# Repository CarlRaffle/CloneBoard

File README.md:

# CloneBoard
CloneBoard - Designed by Carl Raffle for the Clone R1

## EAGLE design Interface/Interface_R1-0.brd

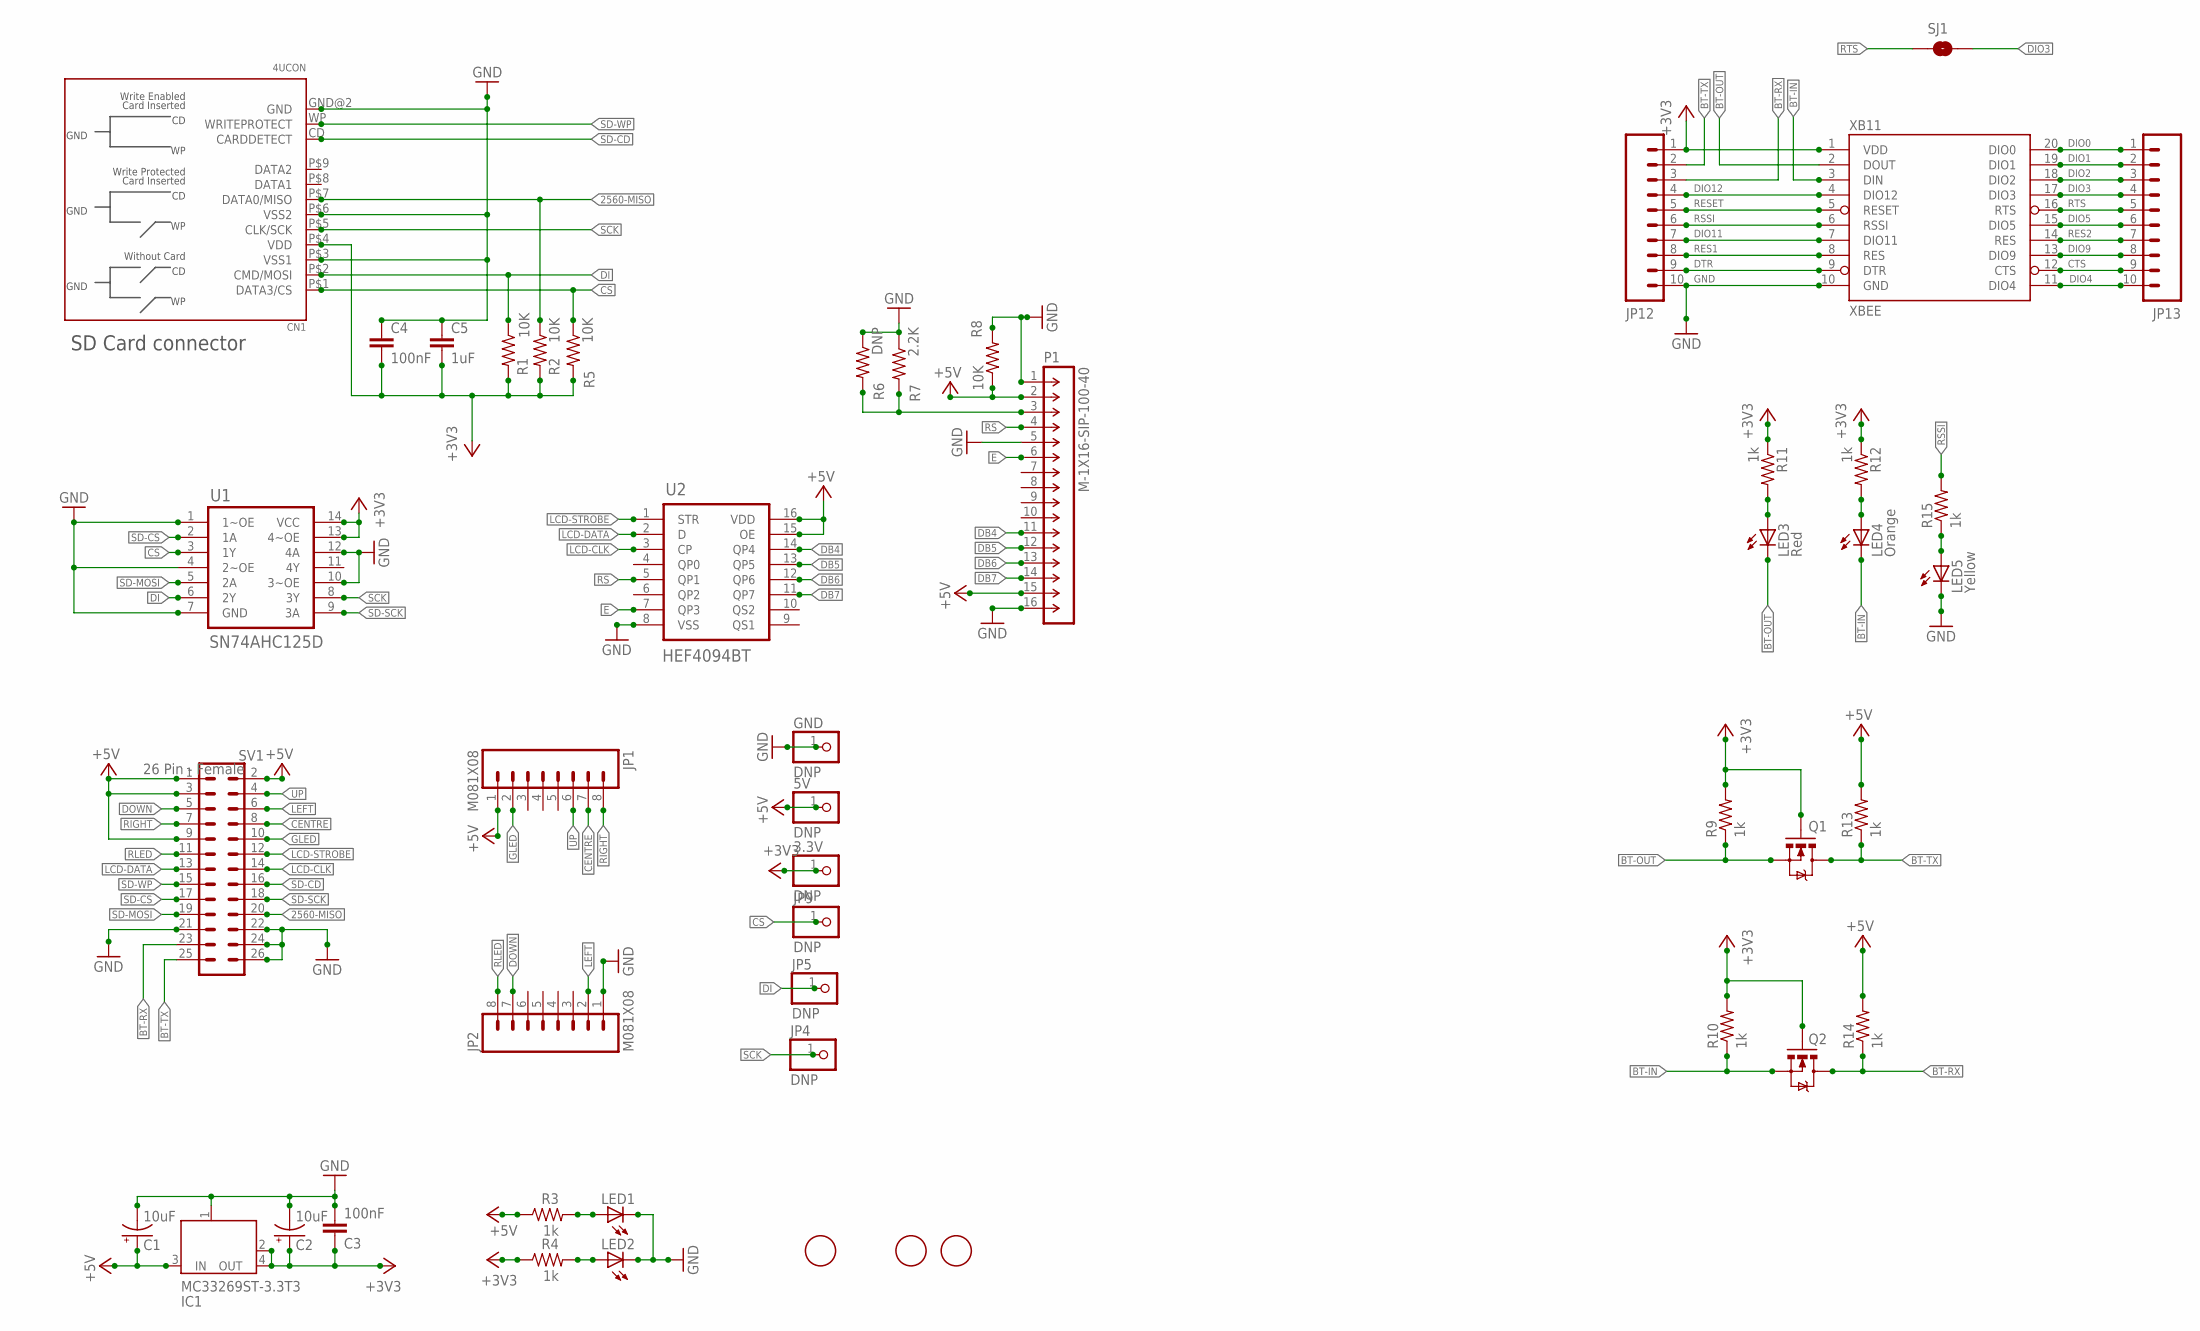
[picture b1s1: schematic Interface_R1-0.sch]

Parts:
3.3V, 5V: DNP; 1X01
C1, C2: 10uF; EIA3216
C3, C4: 100nF; 0805
C5: 1uF; 0805
CN1: 4UCON; SDCARD_SMT_4U19646
GND: DNP; 1X01
IC1: MC33269ST-3.3T3; SOT223
JP1, JP2: M081X08; 1X08
JP3, JP10, JP11: FIDUCIAL1.5X3; FIDUCIAL-1.5X3
JP4, JP5, JP9: DNP; 1X01
JP12, JP13: M100.1; 1X10
LED1: GREEN; LED-0805
LED2: Blue; LED-0805
LED3: Red; LED-0805
LED4: Orange; LED-0805
LED5: Yellow; LED-0805
P1: M-1X16-SIP-100-40; SIP-100-16-40
Q1, Q2: MOSFET-NCHANNELSMD; SOT23-3
R1, R2, R5, R8: 10K; 0805
R3, R4, R9, R10, R11, R12, R13, R14, R15: 1k; 0805
R6: DNP; 0805
R7: 2.2K; 0805
SJ1: SOLDERJUMPERNO; SJ_2S-NO
SV1: 26 Pin - Female; ML26
U1: SN74AHC125D; SOIC127P600X175-14N
U2: HEF4094BT; SOIC127P600X175-16N
XB11: XBEE; XBEE-SILK

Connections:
2560-MISO: CN1.P$7 (DATA0/MISO), R2.1, SV1.20
+3V3: 3.3V.1, C2.A (+), C3.1, C4.2, C5.2, CN1.P$4 (VDD), IC1.2 (OUT), IC1.4 (OUT), JP12.1, Q1.1 (G), Q2.1 (G), R1.2, R2.2, R4.1, R5.2, R9.2, R10.2, R11.1, R12.1, U1.13 (4~OE), U1.14 (VCC), XB11.1 (VDD)
+5V: 5V.1, C1.A (+), IC1.3 (IN), JP1.1, P1.2, P1.15, R3.1, R8.1, R13.2, R14.2, SV1.1, SV1.2, SV1.3, SV1.9, U2.15 (OE), U2.16 (VDD)
BT-IN: LED4.C, Q2.2 (S), R10.1, XB11.3 (DIN)
BT-OUT: LED3.C, Q1.2 (S), R9.1, XB11.2 (DOUT)
BT-RX: JP12.3, Q2.3 (D), R14.1, SV1.23
BT-TX: JP12.2, Q1.3 (D), R13.1, SV1.25
CENTRE: JP1.7, SV1.8
CS: CN1.P$1 (DATA3/CS), JP9.1, R5.1, U1.3 (1Y)
CTS: JP13.9, XB11.12 (CTS)
DB4: P1.11, U2.14 (QP4)
DB5: P1.12, U2.13 (QP5)
DB6: P1.13, U2.12 (QP6)
DB7: P1.14, U2.11 (QP7)
DI: CN1.P$2 (CMD/MOSI), JP5.1, R1.1, U1.6 (2Y)
DIO0: JP13.1, XB11.20 (DIO0)
DIO1: JP13.2, XB11.19 (DIO1)
DIO2: JP13.3, XB11.18 (DIO2)
DIO3: JP13.4, SJ1.2, XB11.17 (DIO3)
DIO4: JP13.10, XB11.11 (DIO4)
DIO5: JP13.6, XB11.15 (DIO5)
DIO9: JP13.8, XB11.13 (DIO9)
DIO11: JP12.7, XB11.7 (DIO11)
DIO12: JP12.4, XB11.4 (DIO12)
DOWN: JP2.7, SV1.5
DTR: JP12.9, XB11.9 (DTR)
E: P1.6, U2.7 (QP3)
GLED: JP1.2, SV1.10
GND: C1.C (-), C2.C (-), C3.2, C4.1, C5.1, CN1.GND@2 (GND), CN1.P$3 (VSS1), CN1.P$6 (VSS2), GND.1, IC1.1 (GND/ADJ), JP2.1, JP12.10, LED1.C, LED2.C, LED5.C, P1.1, P1.5, P1.16, R6.1, R7.1, R8.2, SV1.21, SV1.22, SV1.24, SV1.26, U1.1 (1~OE), U1.4 (2~OE), U1.7 (GND), U1.10 (3~OE), U1.12 (4A), U2.8 (VSS), XB11.10 (GND)
LCD-CLK: SV1.14, U2.3 (CP)
LCD-DATA: SV1.13, U2.2 (D)
LCD-STROBE: SV1.12, U2.1 (STR)
LEFT: JP2.2, SV1.6
unnamed: LED1.A, R3.2
unnamed: LED2.A, R4.2
unnamed: LED3.A, R11.2
unnamed: LED4.A, R12.2
unnamed: LED5.A, R15.1
unnamed: P1.3, R6.2, R7.2
RES1: JP12.8, XB11.8 (RES)
RES2: JP13.7, XB11.14 (RES)
RESET: JP12.5, XB11.5 (RESET)
RIGHT: JP1.8, SV1.7
RLED: JP2.8, SV1.11
RS: P1.4, U2.5 (QP1)
RSSI: JP12.6, R15.2, XB11.6 (RSSI)
RTS: JP13.5, SJ1.1, XB11.16 (RTS)
SCK: CN1.P$5 (CLK/SCK), JP4.1, U1.8 (3Y)
SD-CD: CN1.CD (CARDDETECT), SV1.16
SD-CS: SV1.17, U1.2 (1A)
SD-MOSI: SV1.19, U1.5 (2A)
SD-SCK: SV1.18, U1.9 (3A)
SD-WP: CN1.WP (WRITEPROTECT), SV1.15
UP: JP1.6, SV1.4

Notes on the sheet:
SD Card connector

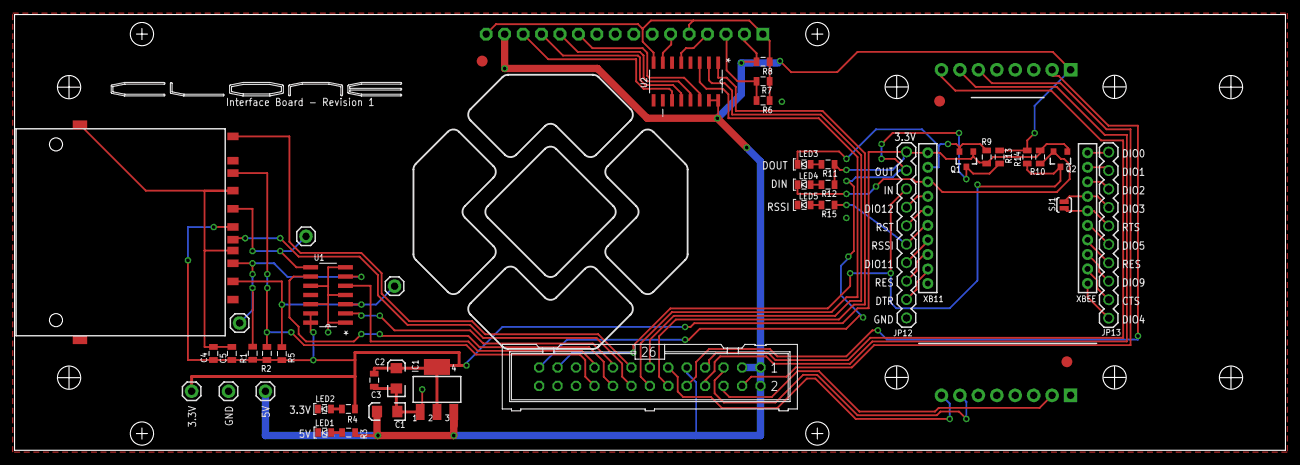
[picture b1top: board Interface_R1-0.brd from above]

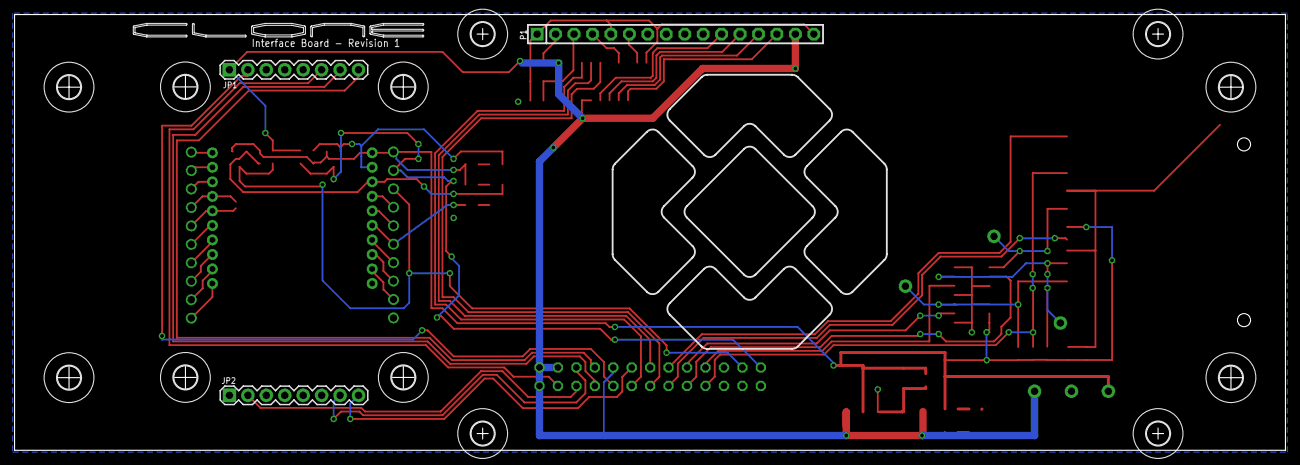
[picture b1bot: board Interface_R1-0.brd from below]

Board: 2 copper layers, 175.0 x 60.0 mm, 60 parts (15 on the bottom side), 54 nets.

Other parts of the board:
$$U$111: 3,2
U$100, U$101, U$102, U$103, U$104, U$105, U$106, U$107, U$108, U$109, U$110: 3,2

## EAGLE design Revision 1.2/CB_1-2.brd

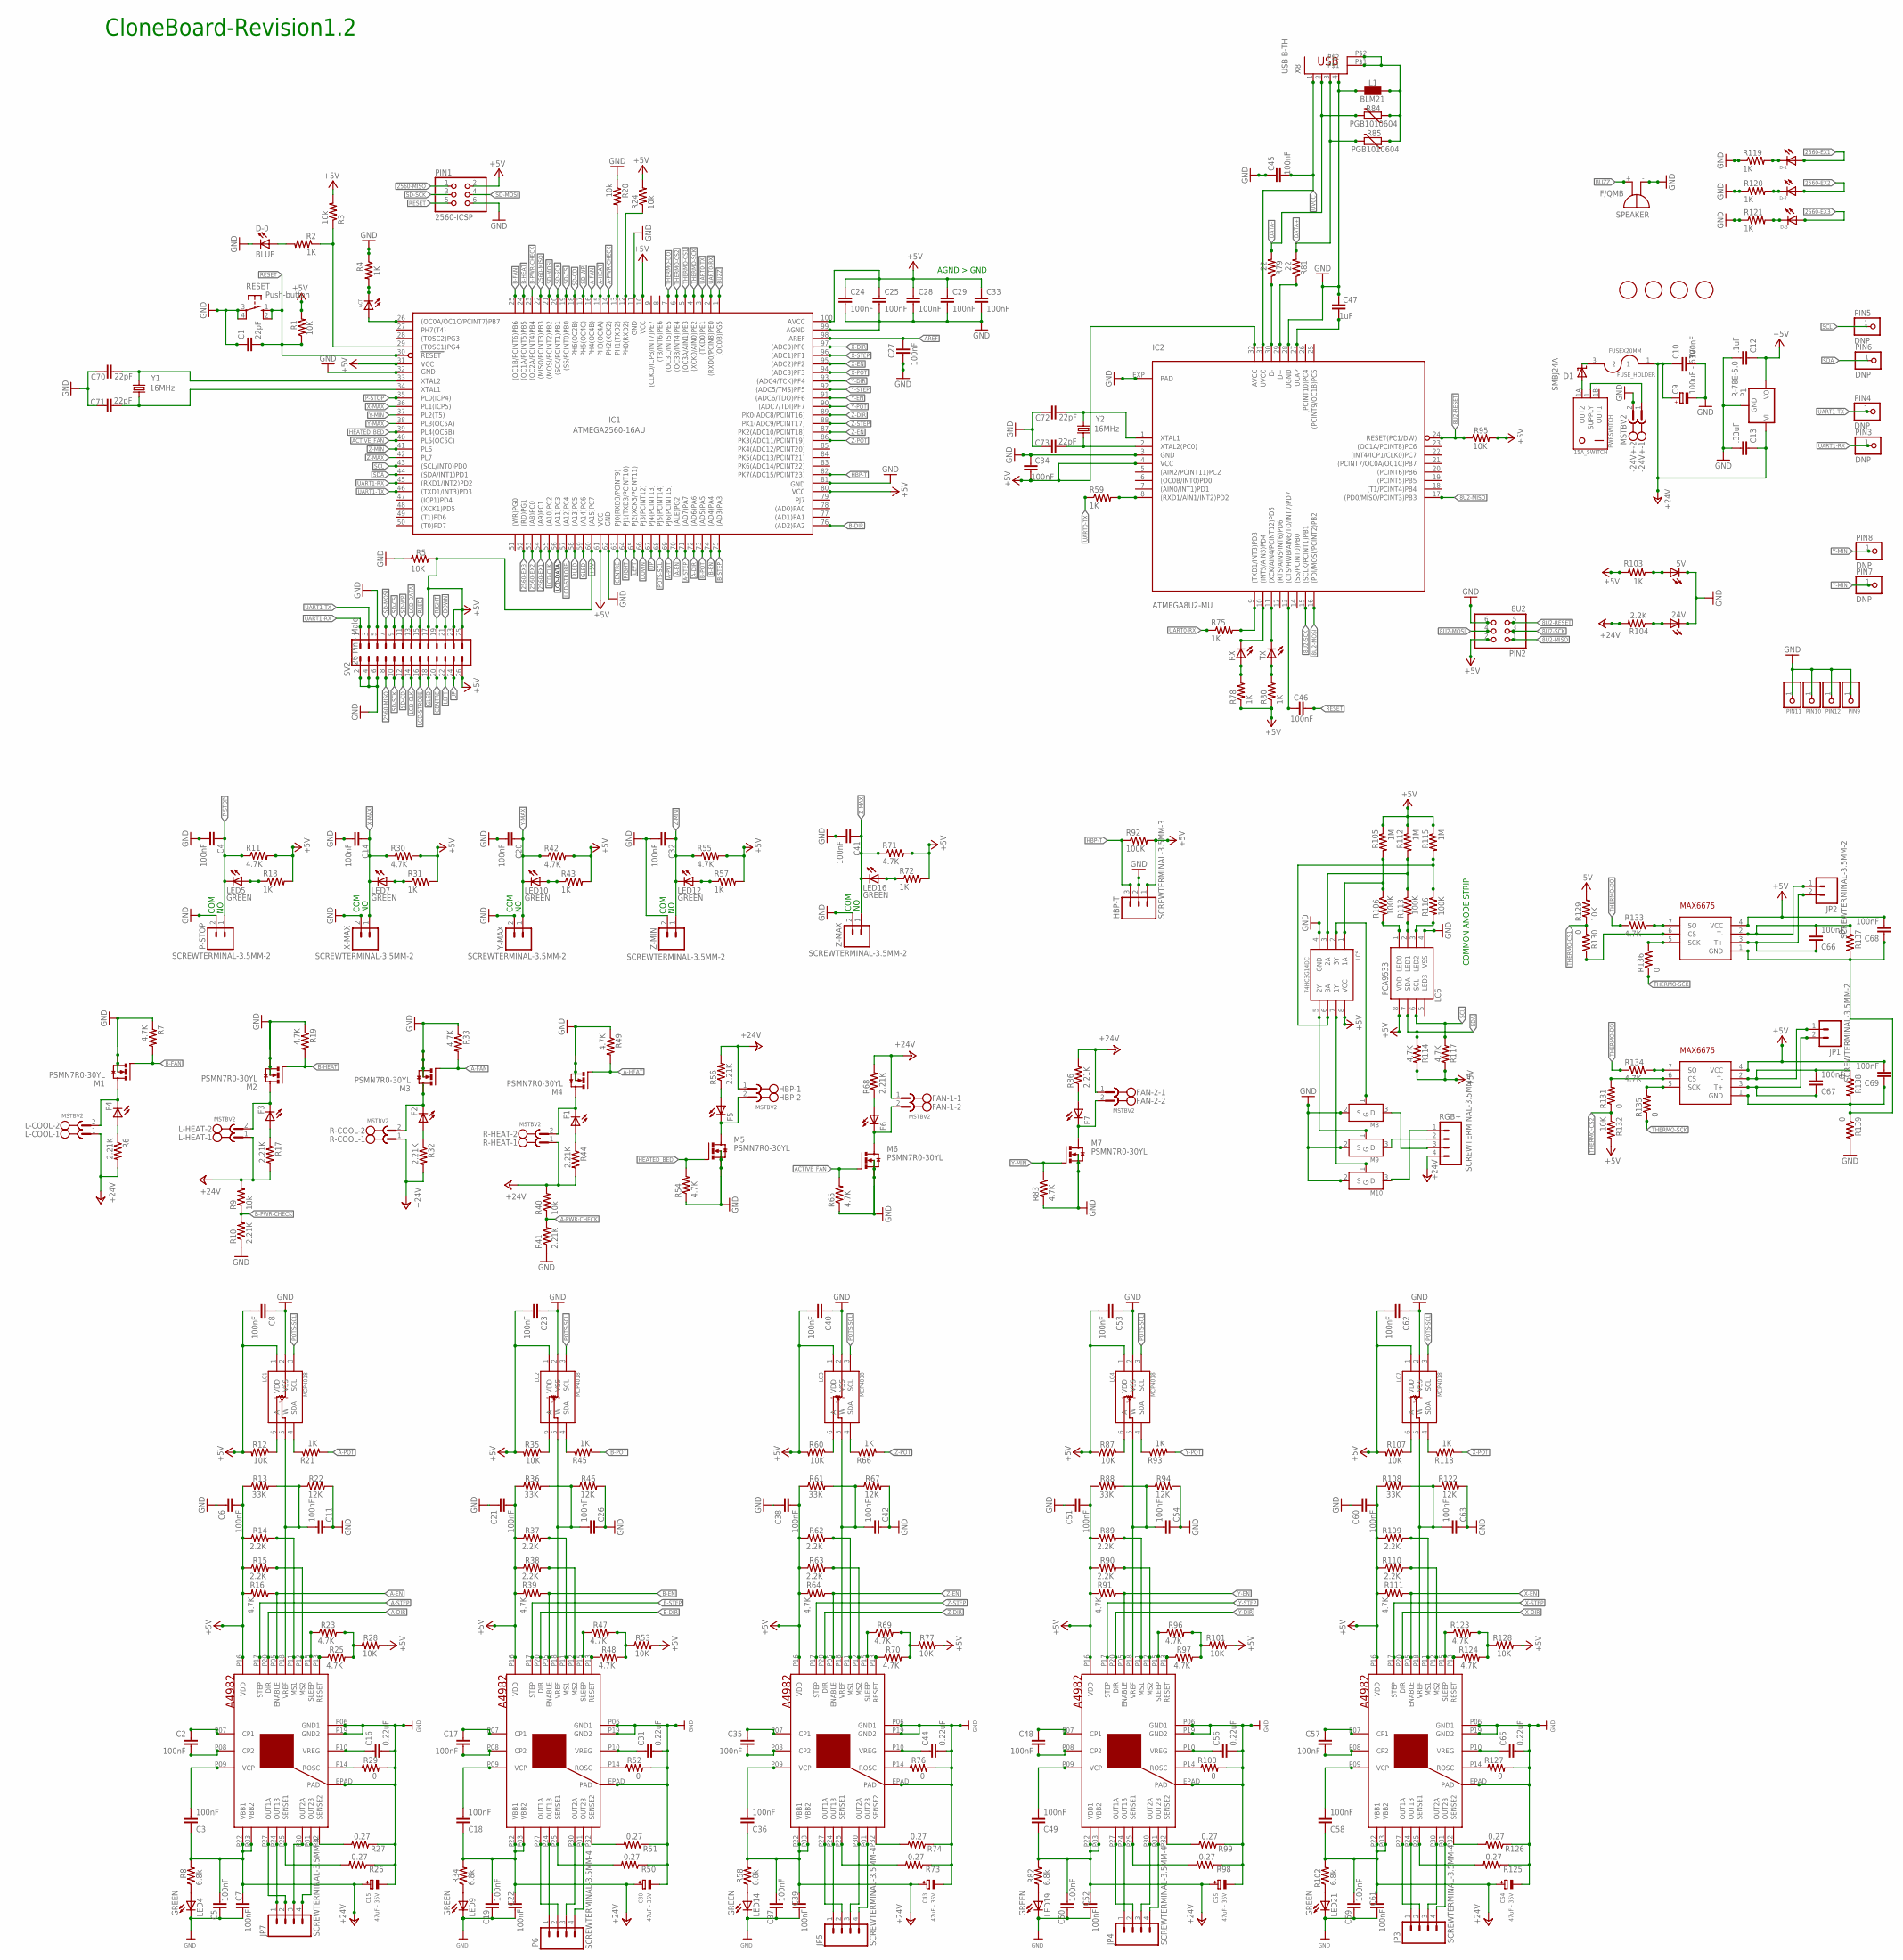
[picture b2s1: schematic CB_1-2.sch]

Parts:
5V: BLUE; LED-0805
15A_SWITCH: PWRSWITCH; D501JT2S2APQF
24V: GREEN; LED-0805
-24V+: MSTBV2
A1, A2, A3, A4, A5: A4982ETSSOP32; ETSSOP32
ACT: BLUE; LED-0805
C1, C70, C71, C72, C73: 22pF; 0805
C2, C3, C4, C5, C6, C7, C8, C10, C11, C14, C17, C18, C19, C20, C21, C22, C23, C24, C25, C26, C27, C28, C29, C32, C33, C34, C35, C36, C37, C38, C39, C40, C41, C42, C45, C46, C48, C49, C50, C51, C52, C53, C54, C57, C58, C59, C60, C61, C62, C63, C66, C67, C68, C69: 100nF; 0805
C9: 100uF - 63V; E3,5-8
C12: .1uF; C0603
C13: .33uF; C0603
C15, C30, C43, C55, C64: 47uF - 35V; EIA7343-31/D-R
C16, C31, C44, C56, C65: 0.22uF; 0805
C47: 1uF; 0805
D1: SMBJ24A; SMBJ
D-0: BLUE; LED-0805
D-1: YELLOW; LED-0805
D-2: ORANGE; LED-0805
D-3: RED; LED-0805
F1, F3, F5: RED; LED-0805
F2, F4, F6, F7: Yellow; LED-0805
FAN-1, FAN-2: MSTBV2
FID1, FID2, FID3, FID4: FIDUCIALMOUNT; FIDUCIA-MOUNT
FUSE_HOLDER: FUSEX20MM; FUSE_5MM
HBP: MSTBV2
HBP-T: SCREWTERMINAL-3.5MM-3
IC1: ATMEGA2560-16AU; TQFP100
IC2: ATMEGA8U2-MU; ATMEL_QFN32
JP1, JP2: SCREWTERMINAL-3.5MM-2
JP3, JP4, JP5, JP6, JP7: SCREWTERMINAL-3.5MM-4; SCREWTERMINAL-3.5MM-4_LOCK
L1: BLM21; 0805
L-COOL: MSTBV2
L-HEAT: MSTBV2
LC1, LC2, LC3, LC4, LC7: MCP4018; SC70-6L
LC5: 74HC3G14DC; VSSOP8
LC6: PCA9533; SO8
LED4, LED5, LED7, LED9, LED10, LED12, LED14, LED16, LED19, LED21: GREEN; LED-0805
M1, M2, M3, M4, M5, M6, M7: PSMN7R0-30YL; SOT669
M8, M9, M10: FDV301N; SOT-23
P1: R-78E-5.0; R-78
P-STOP: SCREWTERMINAL-3.5MM-2
PIN1: 2560-ICSP; 2X03
PIN2: 8U2; 2X03
PIN3, PIN4, PIN5, PIN6, PIN7, PIN8, PIN9, PIN10, PIN11, PIN12: DNP; 1X01
R1, R5, R12, R28, R35, R53, R60, R77, R87, R95, R101, R107, R128, R129, R132: 10K; 0805
R2, R4, R18, R21, R31, R43, R45, R57, R59, R66, R72, R75, R78, R80, R93, R103, R118, R119, R120, R121: 1K; 0805
R3, R9, R20, R24, R40: 10k; 0805
R6, R10, R17, R32, R41, R44, R56, R68, R86: 2.21K; 0805
R7, R11, R16, R19, R23, R25, R30, R33, R39, R42, R47, R48, R49, R54, R55, R64, R65, R69, R70, R71, R83, R91, R96, R97, R111, R114, R117, R123, R124, R133, R134: 4.7K; 0805
R8, R34, R58, R82, R102: 6.8k; 0805
R13, R36, R61, R88, R108: 33K; 0805
R14, R15, R37, R38, R62, R63, R89, R90, R104, R109, R110: 2.2K; 0805
R22, R46, R67, R94, R122: 12K; 0805
R26, R27, R50, R51, R73, R74, R98, R99, R125, R126: 0.27; 0805
R29, R52, R76, R100, R127, R130, R131, R135, R136, R137, R138, R139: 0; 0805
R79, R81: 22; 0805
R84, R85: PGB1010604; CT/CN0603
R92, R106, R113, R116: 100K; 0805
R105, R112, R115: 1M; 0805
R-COOL: MSTBV2
R-HEAT: MSTBV2
RESET: Push-button; B3F-10XX
RGB+: SCREWTERMINAL-3.5MM-4
RX: YELLOW; LED-0805
SPEAKER: F/QMB
SV2: 26 Pin - Male; ML26
T1, T2: MAX6675; SO08
TX: YELLOW; LED-0805
X8: USB B-TH; PN61729
X-MAX: SCREWTERMINAL-3.5MM-2
Y1, Y2: 16MHz; HC49/S
Y-MAX: SCREWTERMINAL-3.5MM-2
Z-MAX: SCREWTERMINAL-3.5MM-2
Z-MIN: SCREWTERMINAL-3.5MM-2

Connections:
8U2-MISO: IC2.17 ((PD0/MISO/PCINT3)PB3), PIN2.1
8U2-MOSI: IC2.16 ((PDI/MOSI/PCINT2)PB2), PIN2.4
8U2-RESET: IC2.24 (RESET(PC1/DW)), PIN2.5, R95.1
8U2-SCK: IC2.15 ((SCLK/PCINT1)PB1), PIN2.3
2560-EX1: D-1.A, IC1.54 ((A9)PC1)
2560-EX2: D-2.A, IC1.53 ((A8)PC0)
2560-EX3: D-3.A, IC1.52 ((RD)PG1)
2560-MISO: IC1.22 ((MISO/PCINT3)PB3), PIN1.1, SV2.8
+5V: A1.P16 (VDD), A2.P16 (VDD), A3.P16 (VDD), A4.P16 (VDD), A5.P16 (VDD), C6.2, C8.2, C12.1, C21.2, C23.2, C24.1, C25.1, C28.1, C29.1, C33.1, C34.2, C38.2, C40.2, C51.2, C53.2, C60.2, C62.2, C68.2, C69.2, HBP-T.1, IC1.10 (VCC), IC1.31 (VCC1), IC1.60 ((A15)PC7), IC1.61 (VCC2), IC1.80 (VCC3), IC1.100 (AVCC), IC2.4 (VCC), IC2.32 (AVCC), LC1.1 (VDD), LC2.1 (VDD), LC3.1 (VDD), LC4.1 (VDD), LC5.8 (VCC), LC6.8 (VDD), LC7.1 (VDD), P1.3 (VO), PIN1.2, PIN2.2, R1.2, R3.2, R5.2, R11.2, R12.2, R13.1, R14.1, R15.1, R16.2, R18.2, R24.2, R28.2, R30.2, R31.2, R35.2, R36.1, R37.1, R38.1, R39.2, R42.2, R43.2, R53.2, R55.2, R57.2, R60.2, R61.1, R62.1, R63.1, R64.2, R71.2, R72.2, R77.2, R78.1, R80.1, R87.2, R88.1, R89.1, R90.1, R91.2, R92.2, R95.2, R101.2, R103.1, R105.1, R107.2, R108.1, R109.1, R110.1, R111.2, R112.1, R114.2, R115.1, R117.2, R128.2, R129.2, R132.2, SV2.17, SV2.23, SV2.25, SV2.26, T1.4 (VCC), T2.4 (VCC)
+24V: A1.P03 (VBB2), A1.P22 (VBB1), A2.P03 (VBB2), A2.P22 (VBB1), A3.P03 (VBB2), A3.P22 (VBB1), A4.P03 (VBB2), A4.P22 (VBB1), A5.P03 (VBB2), A5.P22 (VBB1), C3.1, C5.2, C7.2, C9.+, C10.1, C13.1, C15.+, C18.1, C19.2, C22.2, C30.+, C36.1, C37.2, C39.2, C43.+, C49.1, C50.2, C52.2, C55.+, C58.1, C59.2, C61.2, C64.+, FAN-1.1, FAN-2.1, FUSE_HOLDER.1, HBP.1, L-COOL.1, L-HEAT.1, P1.1 (VI), R6.2, R8.2, R9.2, R17.2, R32.2, R34.2, R40.2, R44.2, R56.2, R58.2, R68.2, R82.2, R86.2, R102.2, R104.2, R-COOL.1, R-HEAT.1, RGB+.4
A-DIR: A1.P20 (DIR), IC1.72 ((AD6)PA6)
A-EN: A1.P05 (ENABLE), IC1.70 ((ALE)PG2), R16.1
A-FAN: IC1.16 (PH4(OC4B)), M3.4 (G), R33.2
A-HEAT: IC1.15 (PH3(OC4A)), M4.4 (G), R49.2
A-POT: IC1.69 (PJ6(PCINT15)), R21.2
A-PWR-CHECK: IC1.14 (PH2(XCK2)), R40.1, R41.2
A-STEP: A1.P17 (STEP), IC1.71 ((AD7)PA7)
ACTIVE_FAN: IC1.40 (PL5(OC5C)), M6.4 (G), R65.2
AREF: C27.1, IC1.98 (AREF)
B-DIR: A2.P20 (DIR), IC1.76 ((AD2)PA2)
B-EN: A2.P05 (ENABLE), IC1.74 ((AD4)PA4), R39.1
B-FAN: IC1.25 ((OC1B/PCINT6)PB6), M1.4 (G), R7.2
B-HEAT: IC1.24 ((OC1A/PCINT5)PB5), M2.4 (G), R19.2
B-POT: IC1.73 ((AD5)PA5), R45.2
B-PWR-CHECK: IC1.23 ((OC2A/PCINT4)PB4), R9.1, R10.2
B-STEP: A2.P17 (STEP), IC1.75 ((AD3)PA3)
BUZZ: IC1.1 ((OC0B)PG5), SPEAKER.+ (-)
CENTRE: IC1.63 (PJ0(RXD3/PCINT9)), SV2.20
CUTOFF-SR-CHECK: IC1.29 ((TOSC1)PG4), R2.1, R3.1
DATA+: R81.2, R85.2, X8.3
DATA-: R79.2, R84.2, X8.2
DOWN: IC1.66 (PJ3(PCINT12)), SV2.21
DTR2: C46.1, IC2.13 ((CTS/HWB/AIN6/TO/INT7)PD7)
GLED: IC1.59 ((A14)PC6), SV2.18
GND: 5V.C, 24V.C, -24V+.2, A1.EPAD (PAD), A1.P06 (GND1), A1.P19 (GND2), A2.EPAD (PAD), A2.P06 (GND1), A2.P19 (GND2), A3.EPAD (PAD), A3.P06 (GND1), A3.P19 (GND2), A4.EPAD (PAD), A4.P06 (GND1), A4.P19 (GND2), A5.EPAD (PAD), A5.P06 (GND1), A5.P19 (GND2), C1.1, C4.2, C5.1, C6.1, C7.1, C8.1, C9.-, C10.2, C11.1, C12.2, C13.2, C14.2, C15.-, C16.2, C19.1, C20.2, C21.1, C22.1, C23.1, C24.2, C25.2, C26.1, C27.2, C28.2, C29.2, C30.-, C31.2, C32.2, C33.2, C34.1, C37.1, C38.1, C39.1, C40.1, C41.2, C42.1, C43.-, C44.2, C45.1, C47.1, C50.1, C51.1, C52.1, C53.1, C54.1, C55.-, C56.2, C59.1, C60.1, C61.1, C62.1, C63.1, C64.-, C65.2, C70.1, C71.1, C72.1, C73.1, D-0.C, HBP-T.2, IC1.11 (GND), IC1.32 (GND1), IC1.62 (GND2), IC1.81 (GND3), IC1.99 (AGND), IC2.3 (GND), IC2.28 (UGND), IC2.EXP (PAD), L1.1, LC1.2 (VSS), LC2.2 (VSS), LC3.2 (VSS), LC4.2 (VSS), LC5.4 (GND), LC6.4 (VSS), LC7.2 (VSS), LED4.C, LED9.C, LED14.C, LED19.C, LED21.C, M1.1 (S), M1.2 (S), M1.3 (S), M2.1 (S), M2.2 (S), M2.3 (S), M3.1 (S), M3.2 (S), M3.3 (S), M4.1 (S), M4.2 (S), M4.3 (S), M5.1 (S), M5.2 (S), M5.3 (S), M6.1 (S), M6.2 (S), M6.3 (S), M7.1 (S), M7.2 (S), M7.3 (S), M8.2 (S), M9.2 (S), M10.2 (S), P1.2 (GND), P-STOP.2, PIN1.6, PIN2.6, PIN9.1, PIN10.1, PIN11.1, PIN12.1, R4.1, R5.1, R7.1, R10.1, R19.1, R20.1, R22.2, R26.1, R27.1, R29.2, R33.1, R41.1, R46.2, R49.1, R50.1, R51.1, R52.2, R54.1, R65.1, R67.2, R73.1, R74.1, R76.2, R83.1, R94.2, R98.1, R99.1, R100.2, R119.1, R120.1, R121.1, R122.2, R125.1, R126.1, R127.2, R139.2, RESET.3, RESET.4 (P1), SPEAKER.- (+), SV2.2, SV2.4, SV2.5, SV2.6, X8.4, X-MAX.2, Y-MAX.2, Z-MAX.2, Z-MIN.2
HBP-T: HBP-T.3, IC1.82 (PK7(ADC15/PCINT23)), R92.1
HEATED_BED: IC1.39 (PL4(OC5B)), M5.4 (G), R54.2
LCD-CLK: IC1.55 ((A10)PC2), SV2.14
LCD-DATA: IC1.56 ((A11)PC3), SV2.13
LCD-STROBE: IC1.57 ((A12)PC4), SV2.16
LEFT: IC1.65 (PJ2(XCK3/PCINT11)), SV2.22
MS6: A1.P12 (MS2), R15.2
MS7: A2.P12 (MS2), R38.2
MS8: A3.P12 (MS2), R63.2
MS9: A4.P12 (MS2), R90.2
MS10: A5.P12 (MS2), R110.2
unnamed: A1.P09 (VCP), C3.2
unnamed: LED4.A, R8.1
unnamed: A1.P10 (VREG), C16.1
unnamed: LC1.6 (A), R12.1
unnamed: LC1.4 (SDA), R21.1
unnamed: R23.2, R25.2, R28.1
unnamed: 5V.A, R103.2
unnamed: A1.P15 (SLEEP), R23.1
unnamed: LED16.A, R72.1
unnamed: 24V.A, R104.1
unnamed: LC6.1 (LED0), R106.2
unnamed: LC6.3 (LED2), R116.2
unnamed: LC6.2 (LED1), R113.2
unnamed: M10.3 (D), RGB+.1
unnamed: M9.3 (D), RGB+.2
unnamed: LED10.A, R43.1
unnamed: F3.A, R17.1
unnamed: LED7.A, R31.1
unnamed: LED5.A, R18.1
unnamed: 15A_SWITCH.1 (SUPPLY), -24V+.1
unnamed: 15A_SWITCH.1A (OUT2), D1.A
unnamed: A1.P13 (RESET), R25.1
unnamed: LC5.6 (3A), R115.2, R116.1
unnamed: LC5.1 (1A), R105.2, R106.1
unnamed: A1.P11 (MS1), R14.2
unnamed: C66.1, JP2.2, T1.3 (T+)
unnamed: M8.3 (D), RGB+.3
unnamed: A1.P18 (VREF), C11.2, LC1.5 (W), R13.2, R22.1
unnamed: LC5.3 (2A), R112.2, R113.1
unnamed: A1.P07 (CP1), C2.1
unnamed: LC5.2 (3Y), M8.1 (G)
unnamed: F3.C, L-HEAT.2, M2.MB (D)
unnamed: C67.1, JP1.2, T2.3 (T+)
unnamed: R130.2, T1.6 (CS)
unnamed: R136.2, T1.5 (SCK)
unnamed: LC5.5 (2Y), M9.1 (G)
unnamed: R131.2, T2.6 (CS)
unnamed: C68.1, C69.1, R137.2, R138.2, R139.1, T1.1 (GND), T2.1 (GND)
unnamed: R135.2, T2.5 (SCK)
unnamed: C66.2, JP2.1, R137.1, T1.2 (T-)
unnamed: F7.A, R86.1
unnamed: F7.C, FAN-2.2, M7.MB (D)
unnamed: LC5.7 (1Y), M10.1 (G)
unnamed: C67.2, JP1.1, R138.1, T2.2 (T-)
unnamed: C71.2, IC1.34 (XTAL1), Y1.1
unnamed: C70.2, IC1.33 (XTAL2), Y1.2
unnamed: R133.2, T1.7 (SO)
unnamed: R134.2, T2.7 (SO)
unnamed: A1.P08 (CP2), C2.2
unnamed: A1.P14 (ROSC), R29.1
unnamed: A2.P09 (VCP), C18.2
unnamed: LED9.A, R34.1
unnamed: A2.P10 (VREG), C31.1
unnamed: LC2.6 (A), R35.1
unnamed: LC2.4 (SDA), R45.1
unnamed: R47.2, R48.2, R53.1
unnamed: A2.P15 (SLEEP), R47.1
unnamed: A2.P13 (RESET), R48.1
unnamed: A2.P11 (MS1), R37.2
unnamed: A2.P18 (VREF), C26.2, LC2.5 (W), R36.2, R46.1
unnamed: A2.P07 (CP1), C17.1
unnamed: A2.P08 (CP2), C17.2
unnamed: A2.P14 (ROSC), R52.1
unnamed: A3.P09 (VCP), C36.2
unnamed: LED14.A, R58.1
unnamed: A3.P10 (VREG), C44.1
unnamed: LC3.6 (A), R60.1
unnamed: LC3.4 (SDA), R66.1
unnamed: R69.2, R70.2, R77.1
unnamed: A3.P15 (SLEEP), R69.1
unnamed: A3.P13 (RESET), R70.1
unnamed: A3.P11 (MS1), R62.2
unnamed: A3.P18 (VREF), C42.2, LC3.5 (W), R61.2, R67.1
unnamed: A3.P07 (CP1), C35.1
unnamed: A3.P08 (CP2), C35.2
unnamed: A3.P14 (ROSC), R76.1
unnamed: A4.P09 (VCP), C49.2
unnamed: LED19.A, R82.1
unnamed: A4.P10 (VREG), C56.1
unnamed: LC4.6 (A), R87.1
unnamed: LC4.4 (SDA), R93.1
unnamed: R96.2, R97.2, R101.1
unnamed: A4.P15 (SLEEP), R96.1
unnamed: A4.P13 (RESET), R97.1
unnamed: A4.P11 (MS1), R89.2
unnamed: A4.P18 (VREF), C54.2, LC4.5 (W), R88.2, R94.1
unnamed: A4.P07 (CP1), C48.1
unnamed: A4.P08 (CP2), C48.2
unnamed: D-1.C, R119.2
unnamed: D-2.C, R120.2
unnamed: A4.P14 (ROSC), R100.1
unnamed: A5.P09 (VCP), C58.2
unnamed: LED21.A, R102.1
unnamed: A5.P10 (VREG), C65.1
unnamed: LC7.6 (A), R107.1
unnamed: LC7.4 (SDA), R118.1
unnamed: R123.2, R124.2, R128.1
unnamed: A5.P15 (SLEEP), R123.1
unnamed: A5.P13 (RESET), R124.1
unnamed: A5.P11 (MS1), R109.2
unnamed: A5.P18 (VREF), C63.2, LC7.5 (W), R108.2, R122.1
unnamed: A5.P07 (CP1), C57.1
unnamed: D-3.C, R121.2
unnamed: ACT.C, R4.2
unnamed: ACT.A, IC1.26 ((OC0A/OC1C/PCINT7)PB7)
unnamed: A5.P08 (CP2), C57.2
unnamed: LED12.A, R57.1
unnamed: A5.P14 (ROSC), R127.1
unnamed: C73.2, IC2.2 (XTAL2(PC0)), Y2.1
unnamed: C72.2, IC2.1 (XTAL1), Y2.2
unnamed: F4.A, R6.1
unnamed: F4.C, L-COOL.2, M1.MB (D)
unnamed: F1.A, R44.1
unnamed: D1.C, FUSE_HOLDER.3 (2)
unnamed: IC1.12 (PH0(RXD2)), R24.1
unnamed: D-0.A, R2.2
unnamed: IC1.13 (PH1(TXD2)), R20.2
unnamed: F1.C, M4.MB (D), R-HEAT.2
unnamed: F2.A, R32.1
unnamed: F2.C, M3.MB (D), R-COOL.2
unnamed: F5.A, R56.1
unnamed: F5.C, HBP.2, M5.MB (D)
unnamed: F6.A, R68.1
unnamed: F6.C, FAN-1.2, M6.MB (D)
unnamed: R78.2, RX.A
unnamed: R80.2, TX.A
unnamed: IC2.10 ((INT5/AIN3)PD4), RX.C
unnamed: IC2.11 ((XCK/AIN4/PCINT12)PD5), TX.C
unnamed: IC2.9 ((TXD1/INT3)PD3), R75.2
unnamed: IC2.8 ((RXD1/AIN1/INT2)PD2), R59.2
unnamed: IC2.30 (D-), R79.1
OUT1A5: A1.P27 (OUT1A), JP7.2
OUT1A6: A2.P27 (OUT1A), JP6.2
OUT1A7: A3.P27 (OUT1A), JP5.2
OUT1A8: A4.P27 (OUT1A), JP4.2
OUT1A9: A5.P27 (OUT1A), JP3.2
OUT1B5: A1.P24 (OUT1B), JP7.1
OUT1B6: A2.P24 (OUT1B), JP6.1
OUT1B7: A3.P24 (OUT1B), JP5.1
OUT1B8: A4.P24 (OUT1B), JP4.1
OUT1B9: A5.P24 (OUT1B), JP3.1
OUT2A5: A1.P30 (OUT2A), JP7.3
OUT2A6: A2.P30 (OUT2A), JP6.3
OUT2A7: A3.P30 (OUT2A), JP5.3
OUT2A8: A4.P30 (OUT2A), JP4.3
OUT2A9: A5.P30 (OUT2A), JP3.3
OUT2B5: A1.P01 (OUT2B), JP7.4
OUT2B6: A2.P01 (OUT2B), JP6.4
OUT2B7: A3.P01 (OUT2B), JP5.4
OUT2B8: A4.P01 (OUT2B), JP4.4
OUT2B9: A5.P01 (OUT2B), JP3.4
P-STOP: C4.1, IC1.35 (PL0(ICP4)), LED5.C, P-STOP.1, R11.1
POTS-SCL: IC1.68 (PJ5(PCINT14)), LC1.3 (SCL), LC2.3 (SCL), LC3.3 (SCL), LC4.3 (SCL), LC7.3 (SCL)
RD+2: IC2.29 (D+), R81.1
RESET: C1.2, C46.2, IC1.30 (RESET), PIN1.5, R1.1, RESET.1 (S), RESET.2 (S1)
RIGHT: IC1.64 (PJ1(TXD3/PCINT10)), SV2.19
RLED: IC1.58 ((A13)PC5), SV2.15
SCL: IC1.43 ((SCL/INT0)PD0), LC6.6 (SCL), PIN5.1, R117.1
SD-CD: IC1.18 (PH6(OC2B)), SV2.12
SD-CS: IC1.19 ((SS/PCINT0)PB0), SV2.9
SD-MOSI: IC1.21 ((MOSI/PCINT2)PB2), PIN1.4, SV2.7
SD-SCK: IC1.20 ((SCK/PCINT1)PB1), PIN1.3, SV2.10
SD-WP: IC1.17 (PH5(OC4C)), SV2.11
SDA: IC1.44 ((SDA/INT1)PD1), LC6.7 (SDA), PIN6.1, R114.1
SENSE11: A1.P25 (SENSE1), R26.2
SENSE12: A1.P32 (SENSE2), R27.2
SENSE13: A2.P25 (SENSE1), R50.2
SENSE14: A2.P32 (SENSE2), R51.2
SENSE15: A3.P25 (SENSE1), R73.2
SENSE16: A3.P32 (SENSE2), R74.2
SENSE17: A4.P25 (SENSE1), R98.2
SENSE18: A4.P32 (SENSE2), R99.2
SENSE19: A5.P25 (SENSE1), R125.2
SENSE20: A5.P32 (SENSE2), R126.2
THERMO-CS1: IC1.5 ((OC3A/AIN1)PE3), R129.1, R130.1
THERMO-CS2: IC1.6 ((OC3B/INT4)PE4), R131.1, R132.1
THERMO-DO: IC1.7 ((OC3C/INT5)PE5), R133.1, R134.1
THERMO-SCK: IC1.4 ((XCK0/AIN0)PE2), R135.1, R136.1
UART0-RX: IC1.2 ((RXD0/PCIN8)PE0), R75.1
UART0-TX: IC1.3 ((TXD0)PE1), R59.1
UART1-RX: IC1.45 ((RXD1/INT2)PD2), PIN3.1, SV2.1
UART1-TX: IC1.46 ((TXD1/INT3)PD3), PIN4.1, SV2.3
UP: IC1.67 (PJ4(PCINT13)), SV2.24
USHIELD2: L1.2, R84.1, R85.1, X8.P$1, X8.P$2
UVCC: C45.2, IC2.31 (UVCC), X8.1
VUCAP2: C47.2, IC2.27 (UCAP)
X-DIR: A5.P20 (DIR), IC1.97 ((ADC0)PF0)
X-EN: A5.P05 (ENABLE), IC1.95 ((ADC2)PF2), R111.1
X-MAX: C14.1, IC1.36 (PL1(ICP5)), LED7.C, R30.1, X-MAX.1
X-POT: IC1.94 ((ADC3)PF3), R118.2
X-STEP: A5.P17 (STEP), IC1.96 ((ADC1)PF1)
Y-DIR: A4.P20 (DIR), IC1.93 ((ADC4/TCK)PF4)
Y-EN: A4.P05 (ENABLE), IC1.91 ((ADC6/TDO)PF6), R91.1
Y-MAX: C20.1, IC1.38 (PL3(OC5A)), LED10.C, R42.1, Y-MAX.1
Y-MIN: IC1.37 (PL2(T5)), M7.4 (G), PIN7.1, PIN8.1, R83.2
Y-POT: IC1.90 ((ADC7/TDI)PF7), R93.2
Y-STEP: A4.P17 (STEP), IC1.92 ((ADC5/TMS)PF5)
Z-DIR: A3.P20 (DIR), IC1.89 (PK0(ADC8/PCINT16))
Z-EN: A3.P05 (ENABLE), IC1.87 (PK2(ADC10/PCINT18)), R64.1
Z-MAX: C41.1, IC1.42 (PL7), LED16.C, R71.1, Z-MAX.1
Z-MIN: C32.1, IC1.41 (PL6), LED12.C, R55.1, Z-MIN.1
Z-POT: IC1.86 (PK3(ADC11/PCINT19)), R66.2
Z-STEP: A3.P17 (STEP), IC1.88 (PK1(ADC9/PCINT17))

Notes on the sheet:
CloneBoard-Revision1.2
AGND > GND
COMMON ANODE STRIP
COM

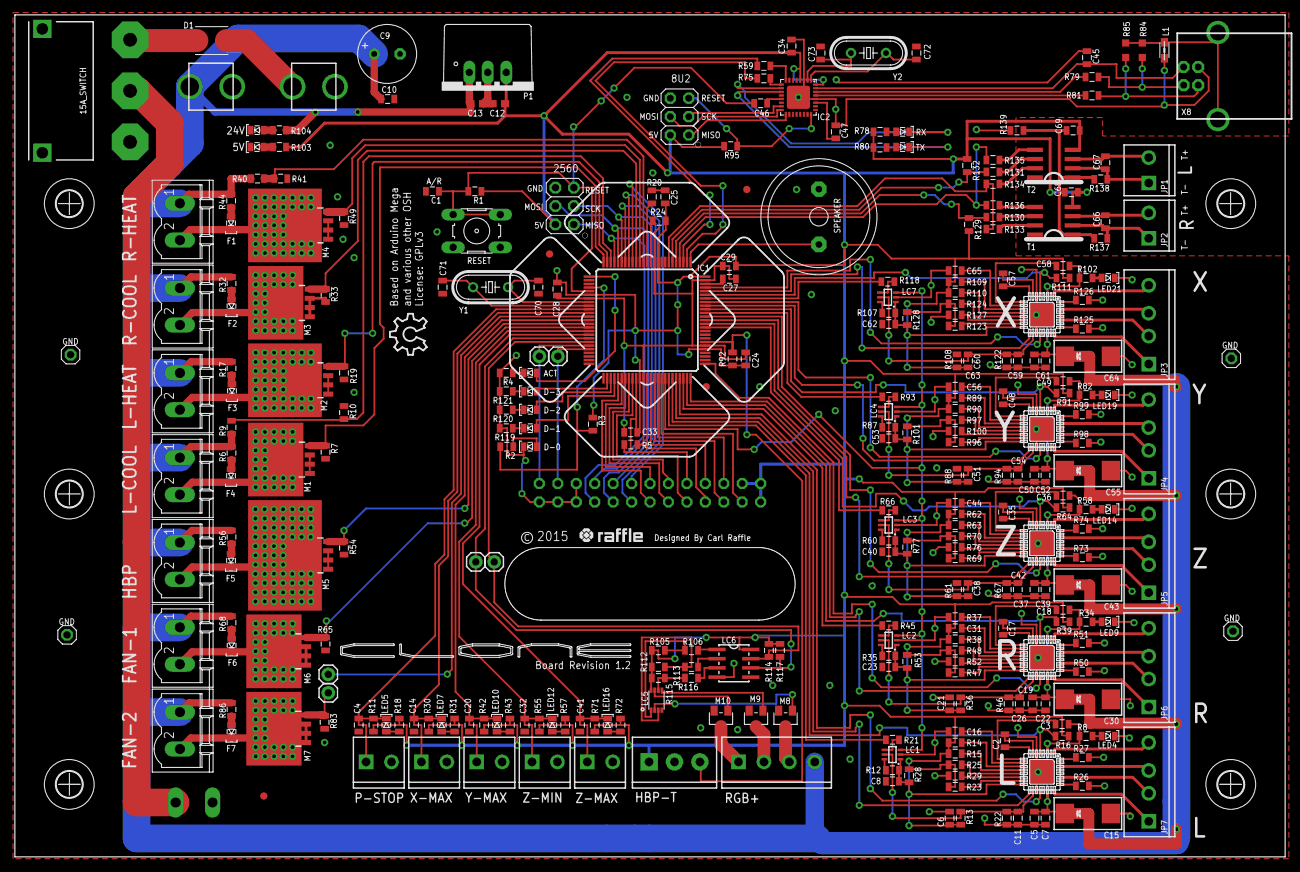
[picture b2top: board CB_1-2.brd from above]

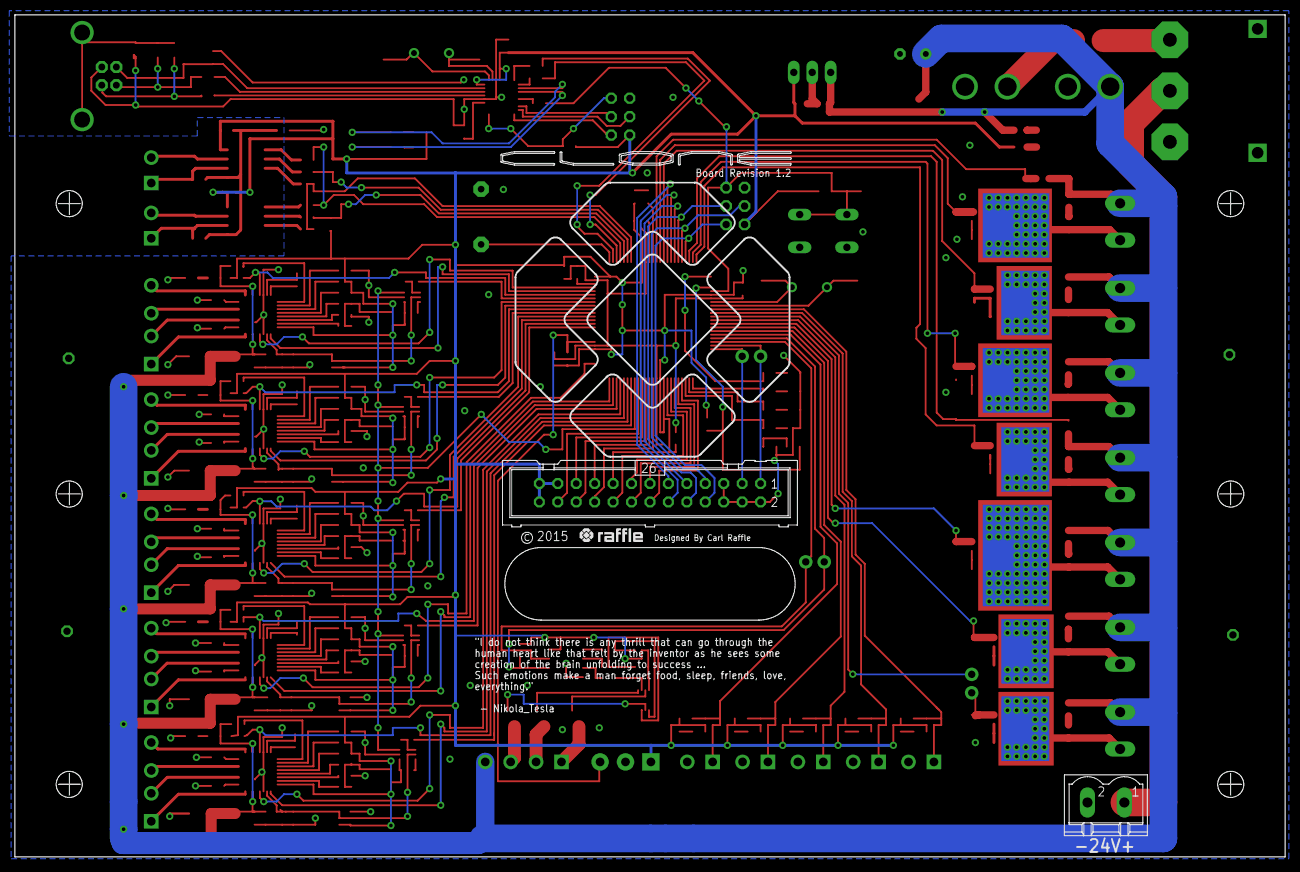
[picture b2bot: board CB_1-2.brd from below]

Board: 2 copper layers, 175.0 x 116.0 mm, 320 parts (2 on the bottom side), 249 nets.

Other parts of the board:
LOGO2: OSHW_LOGO_10MILX0200-NT; OSHW_10X200_NOTEXT
U$1, U$2, U$3, U$4, U$5, U$6: 3,6

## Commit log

2015-06-17 Readme Update
    Readme Update
2015-06-18 CloneBoard Revision 1.2
    CloneBoard Revision 1.2
2015-06-18 Revision 1.2
    CloneBoard Revision 1.2
2015-06-18 Readme
    Readme.md
2015-06-18 Interface R1.0
    CloneBoard Interface Revision 1.0
2015-06-18 CloneBoard
    CloneBoard

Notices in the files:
Revision 1.2/CB_1-2.brd:
License: GPLv3
parts and their libraries:
SparkFun: Licensing: CC v3.0 Share-Alike You are welcome to use this library for commercial purposes.
con-headers-jp: Copyright (C) 2008, Bob Starr
SparkFun-Capacitors: Licensing: Creative Commons ShareAlike 4.0 International - https://creativecommons.org/licenses/by-sa/4.0
